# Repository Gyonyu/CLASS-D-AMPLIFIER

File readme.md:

# Class-D Audio Amplifier v2.0 
An high-efficiency, digitally controlled Class-D audio power amplifier based on a **Full-Bridge (Bridge-Tied Load / BTL)** power stage. Version 2.0 introduces high-resolution stereo analog audio acquisition using the **PCM1808 24-bit ADC**, interfaced to an STM32 microcontroller configured via STM32Cube peripheral drivers and built using a CMake workflow in VS Code.
* **Power Stage Topology:** Full-Bridge (BTL) output stage offering doubled voltage swing across the load without requiring negative supply rails.
* **Audio Frontend (v2.0 Upgrade):** **PCM1808** 24-bit, 96 kHz stereo single-ended audio ADC sending digital audio over **$I^2S$ / DMA**.
* **Microcontroller Core:** STM32 MCU executing real-time signal handling, PWM dead-time generation, and digital modulation.
* **Filter Stage:** Differential 2nd-order LC reconstruction filter optimized for $4\Omega$ and $8\Omega$ speaker impedances.
* **Toolchain & Build System:** Firmware structured using **STM32CubeMX / Cube HAL**, configured for compilation with **CMake**, **Ninja**, and **GCC Arm Embedded** in **VS Code**.
* **PCB Hardware:** 2-layer optimized PCB layout engineered for minimal loop inductance, ground isolation between analog and digital/power sections, and EMI mitigation.

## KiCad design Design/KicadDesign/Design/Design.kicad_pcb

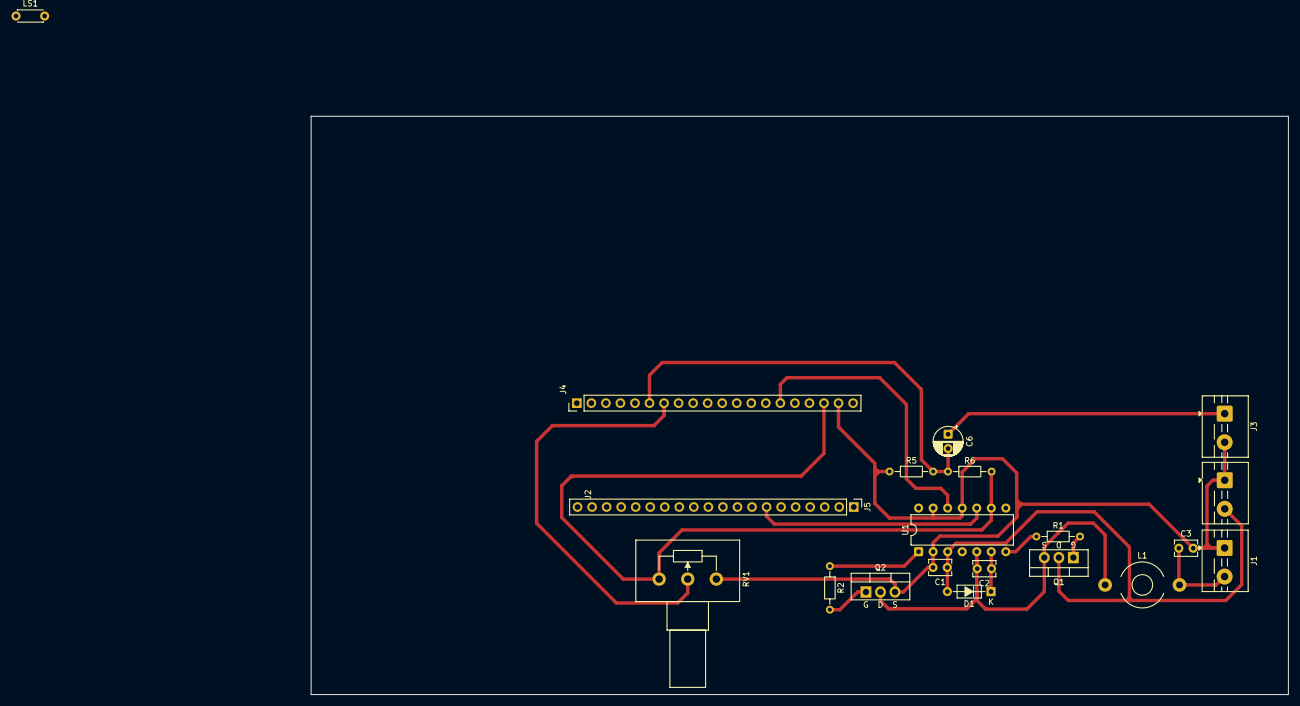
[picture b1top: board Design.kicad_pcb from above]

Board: 2 copper layers, 170.7 x 101.0 mm, 20 parts (0 on the bottom side), 15 nets.

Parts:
C1, C2, C3: 470n; C_Disc_D3.8mm_W2.6mm_P2.50mm
C6: 4.7u; CP_Radial_D5.0mm_P2.50mm
D1: 1N4148; D_DO-35_SOD27_P7.62mm_Horizontal
J1: Speaker; TerminalBlock_MaiXu_MX126-5.0-02P_1x02_P5.00mm
J2: SourceSupply; TerminalBlock_MaiXu_MX126-5.0-02P_1x02_P5.00mm
J3: Jack 3.5 mm; TerminalBlock_MaiXu_MX126-5.0-02P_1x02_P5.00mm
J4, J5: Conn_01x20_Socket; PinHeader_1x20_P2.54mm_Vertical
L1: L; L_Toroid_Horizontal_D7.8mm_P13.00mm_Diameter9-5mm_Amidon-T30
LS1: Speaker; C_Disc_D4.3mm_W1.9mm_P5.00mm
Q1, Q2: IRLZ44N; TO-220-3_Vertical_GDS
R1, R2: 22; R_Axial_DIN0204_L3.6mm_D1.6mm_P7.62mm_Horizontal
R5, R6: 10k; R_Axial_DIN0204_L3.6mm_D1.6mm_P7.62mm_Horizontal
RV1: 20K; Potentiometer_Alps_RK163_Single_Horizontal
U1: IR2110; DIP-14_W7.62mm

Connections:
3.3V: J4.18, R6.2, RV1.1, U1.9 (VDD)
12V: C1.1, D1.2 (A), J2.2, Q1.2 (D), U1.3 (VCC)
A0 ADC1: C6.2, J4.6, R5.2, R6.1
A1 ADC2: J4.7, RV1.2
A10 PWM: J5.7, U1.10 (HIN)
B1 PWM_N: J4.15, U1.12 (LIN)
GND: C1.2, C3.2, J1.1, J2.1, J3.2, J4.19, Q2.3 (S), R5.1, RV1.3, U1.2 (COM), U1.11 (SD), U1.13 (VSS)
unnamed: C3.1, J1.2, L1.2
unnamed: C6.1, J3.1
unnamed: Q1.1 (G), R1.2
unnamed: C2.2, L1.1, Q1.3 (S), Q2.2 (D), U1.5 (VS)
unnamed: Q2.1 (G), R2.2
unnamed: R1.1, U1.7 (HO)
unnamed: R2.1, U1.1 (LO)
VB: C2.1, D1.1 (K), U1.6 (VB)

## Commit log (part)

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2026-05-16 OPtimization
2026-05-19 Sampling implemented correctly
2026-05-19 Volume control
2026-05-19 Fixed volume control
2026-05-20 Added Design of Class D amplifier, TODOs: Add STM footprint, Add Caps on VB
2026-05-20 Added Caps on VB TODO: Add STM32H523cet6 Footprint
2026-05-21 Fixed little performance issues
2026-05-22 Added Resistors
2026-05-22 Added LC Filter
2026-05-22 Fixed volume issues
2026-05-22 Added NG-Pill
2026-05-25 Autorouted TODO: Check Autoroute traces
2026-05-25 Minor fixes on traces
2026-05-25 Updated Kicad (9.0->10.0)
2026-06-03 Updated pin B0->B1 A9->A10
2026-06-04 Minor fixes on PCB
2026-06-05 Added the first part of inverter
2026-06-06 Added the bp proyect
2026-06-09 correctedclock with 25mhz bp
2026-06-09 Added Report and Updated Caps on Design
